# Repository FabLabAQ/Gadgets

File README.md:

# PCBs courtesy of [CMT Energia Dinamica](http://www.cmtenergiadinamica.it/)

## [Tutorial italiano](http://www.fablaquila.org/tutorial/come-assemblare-spille-circuito/)
## [English tutorial](https://create.arduino.cc/projecthub/fablabaq/led-matrix-display-badge-280cfb?ref=team&ref_id=fablabaq&offset=0)

## ATtiny LoRa Node
### top

### bottom

## Ladybug bristlebot

### Final version images

### top

### bottom

## Kids LED badge

### top

### bottom

## LED matrix badge with ATtiny

### top

### bottom

## ATtiny DIY badge

### top

### bottom

## LED matrix printable PCB

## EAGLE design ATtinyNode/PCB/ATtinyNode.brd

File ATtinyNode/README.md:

# ATtiny LoRa node 

A minimal ATtiny85-based LoRaWAN node

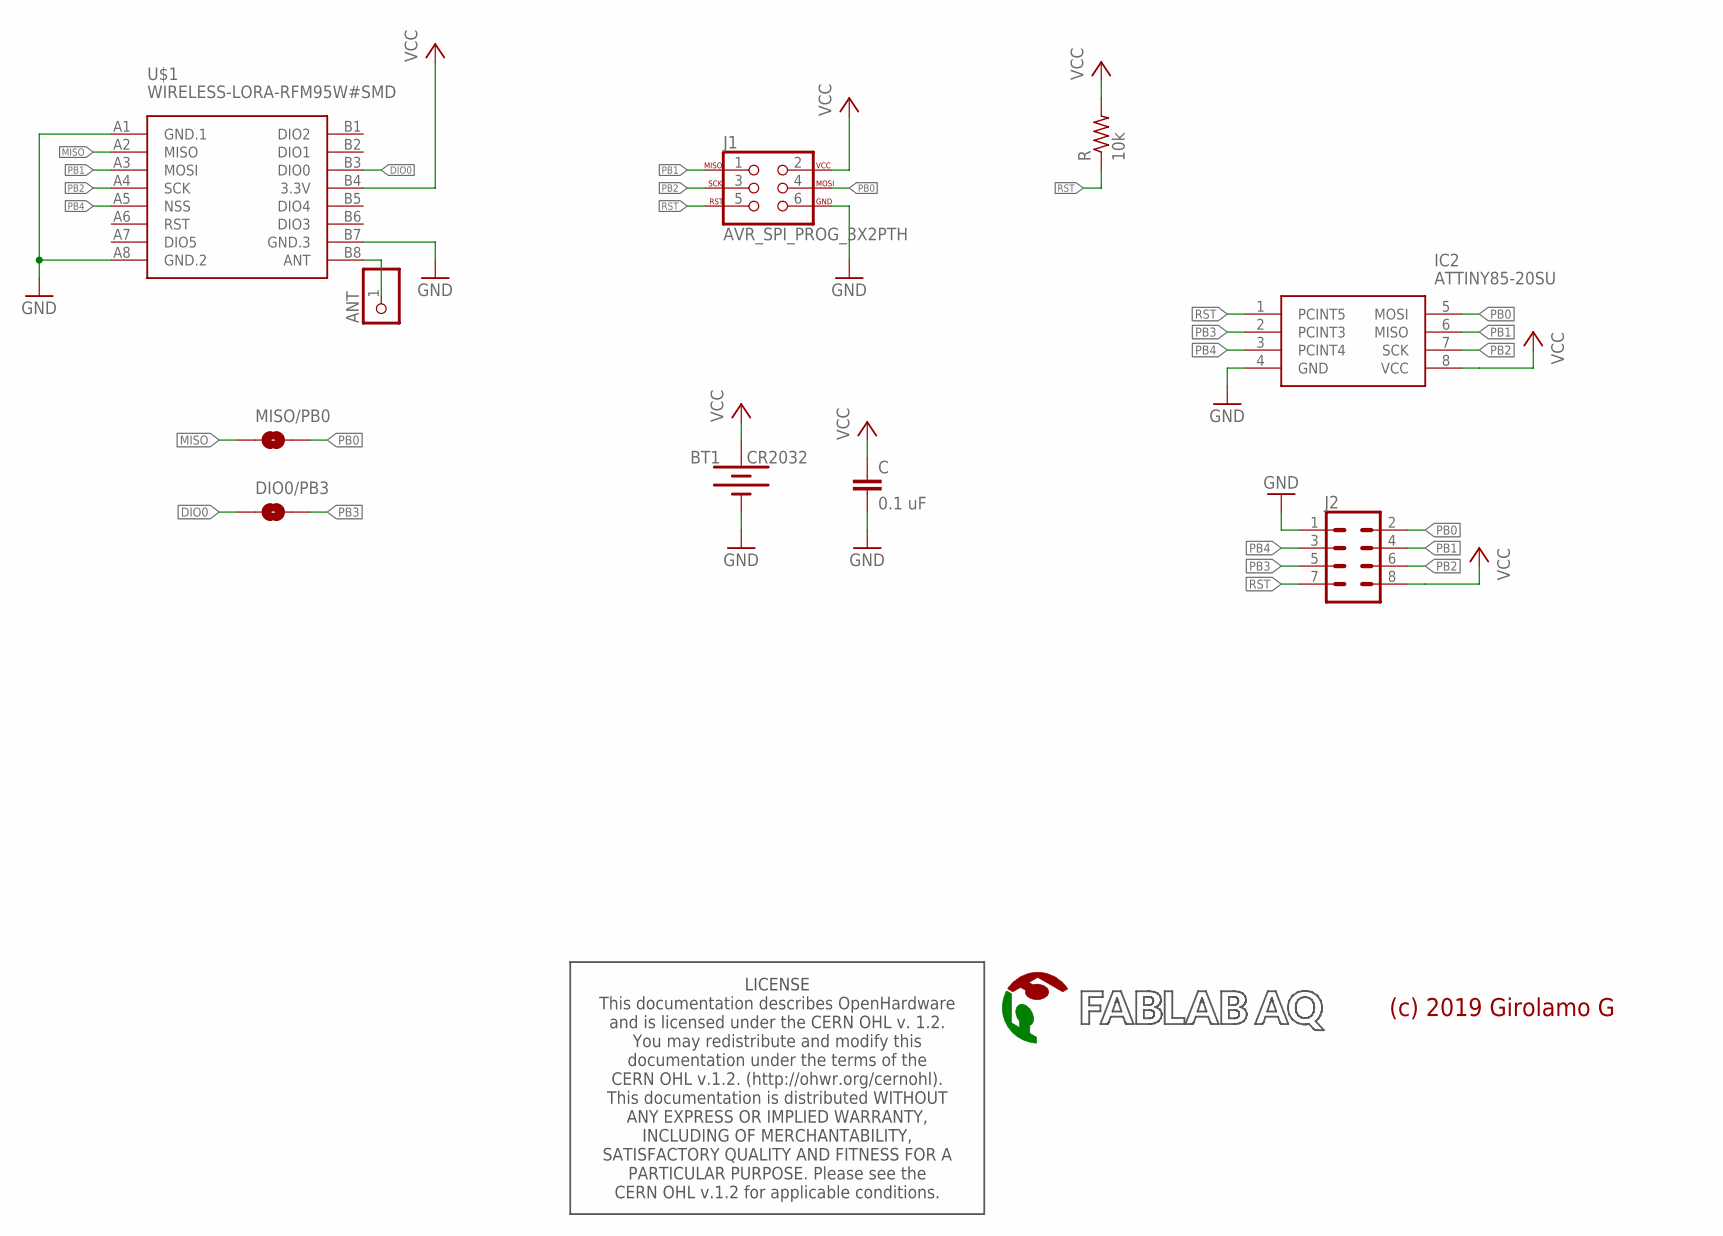
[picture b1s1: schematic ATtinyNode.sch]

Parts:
ANT: PINHD-1X1CB; 1X01-CLEANBIG
BT1: CR2032; BATTCOM_20MM_PTH
C: 0.1 uF; C0805
DIO0/PB3: JUMPER-SMT_2_NO_SILK; SMT-JUMPER_2_NO_SILK
IC2: ATTINY85-20SU; SOT127P798X216-8N
J1: AVR_SPI_PROG_3X2PTH; 2X3
J2: CONN_04X2; 2X4
MISO/PB0: JUMPER-SMT_2_NO_SILK; SMT-JUMPER_2_NO_SILK
R: 10k; R0805
U$1: WIRELESS-LORA-RFM95W#SMD
U$2: FABLABAQ_LOGONONE; NONE
U$3: CERN_OHL_1.2; DOC_CERN_OHL_1.2

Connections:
ANT: ANT.1, U$1.B8 (ANT)
DIO0: DIO0/PB3.1, U$1.B3 (DIO0)
GND: BT1.2 (-), C.2, IC2.4 (GND), J1.6, J2.1, U$1.A1 (GND.1), U$1.A8 (GND.2), U$1.B7 (GND.3)
MISO: MISO/PB0.1, U$1.A2 (MISO)
PB0: IC2.5 (MOSI), J1.4, J2.2, MISO/PB0.2
PB1: IC2.6 (MISO), J1.1, J2.4, U$1.A3 (MOSI)
PB2: IC2.7 (SCK), J1.3, J2.6, U$1.A4 (SCK)
PB3: DIO0/PB3.2, IC2.2 (PCINT3), J2.5
PB4: IC2.3 (PCINT4), J2.3, U$1.A5 (NSS)
RST: IC2.1 (PCINT5), J1.5, J2.7, R.1
VCC: BT1.1 (+), C.1, IC2.8 (VCC), J1.2, J2.8, R.2, U$1.B4 (3.3V)

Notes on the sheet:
(c) 2019 Girolamo G

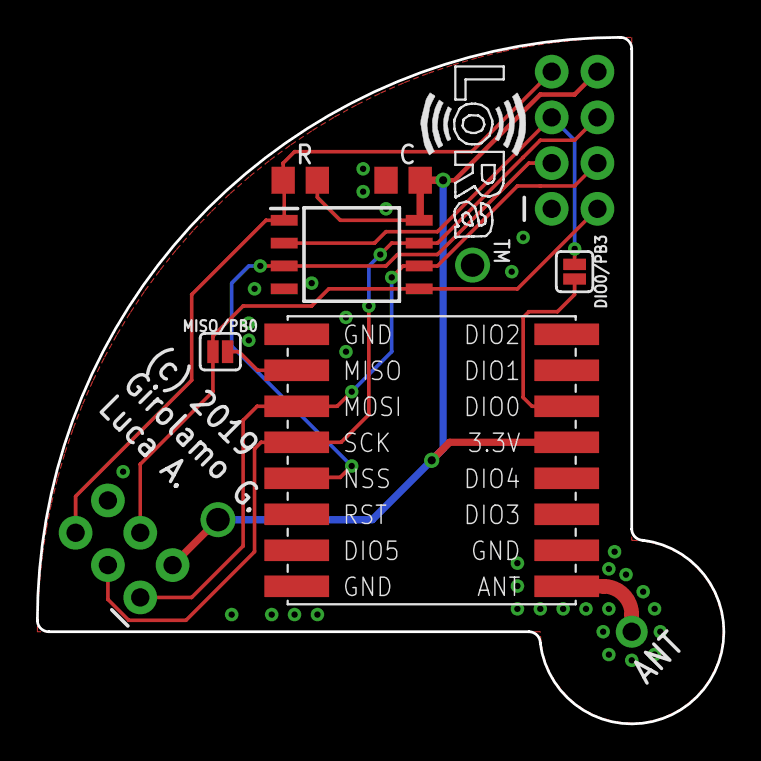
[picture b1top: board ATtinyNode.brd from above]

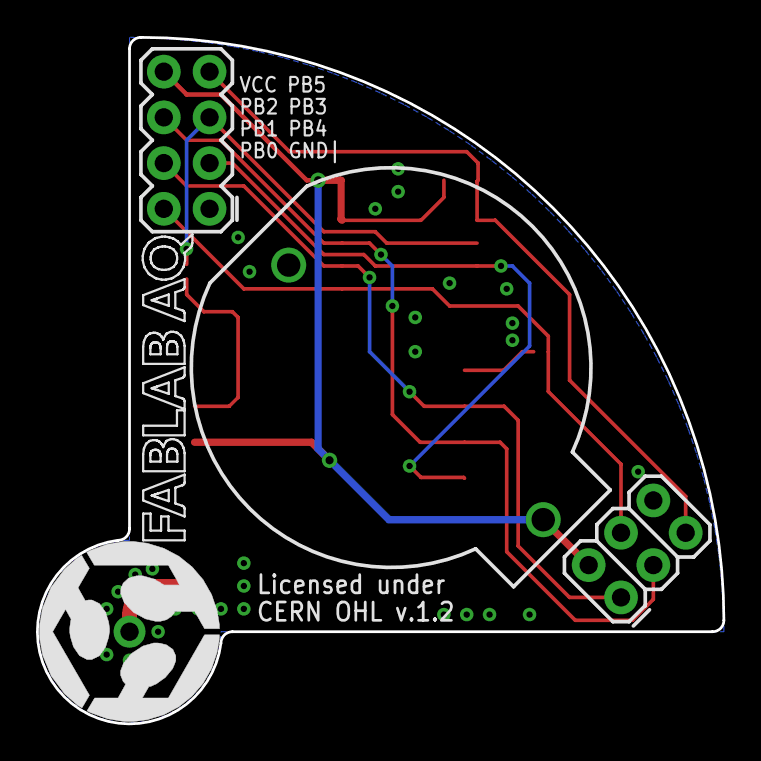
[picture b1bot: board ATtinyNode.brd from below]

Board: 2 copper layers, 38.1 x 38.1 mm, 12 parts (4 on the bottom side), 11 nets.

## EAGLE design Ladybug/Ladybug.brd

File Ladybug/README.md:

## Ladybug bristlebot

### Final version images

### top

### bottom

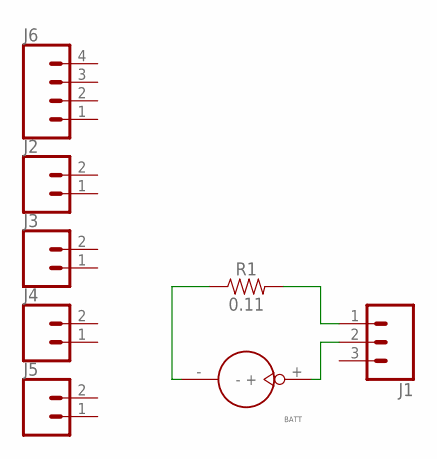
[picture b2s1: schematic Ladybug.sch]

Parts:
BATT: BATTERY_1236_C
J1: CONN_03LOCK; 1X03_LOCK
J2, J3, J4, J5: CONN_02; 1X02
J6: CONN_04; 1X04
R1: 0.11; 2010

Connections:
unnamed: BATT.-, R1.1
unnamed: J1.1, R1.2
unnamed: BATT.+, J1.2

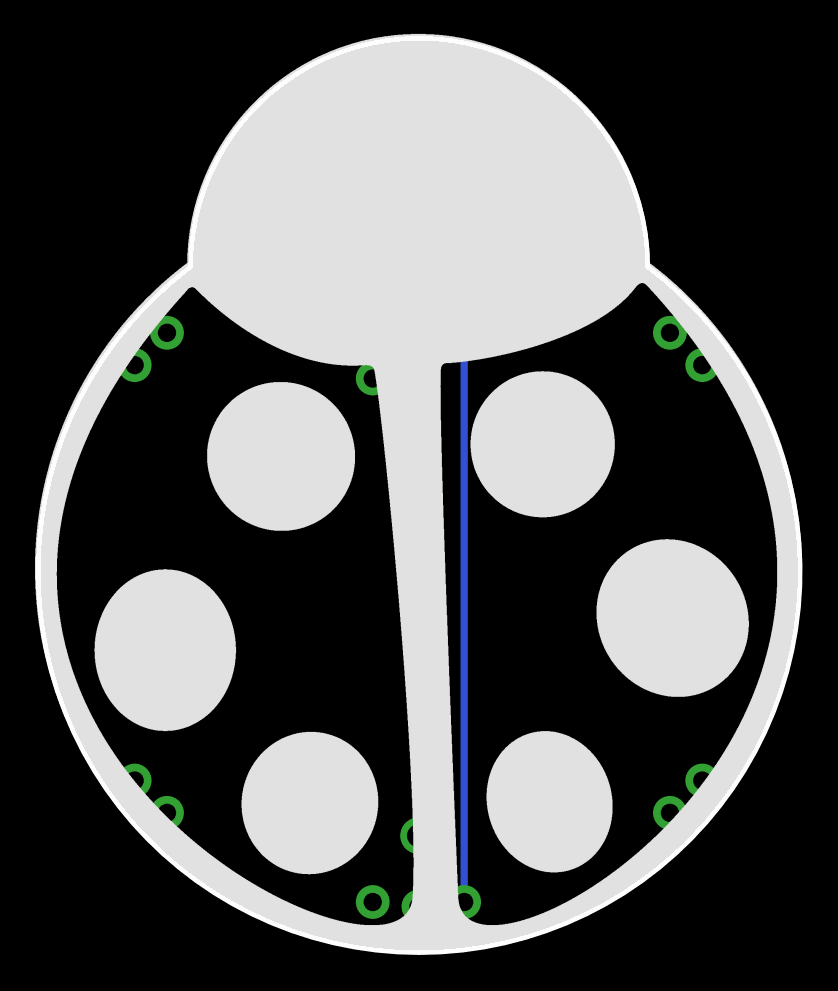
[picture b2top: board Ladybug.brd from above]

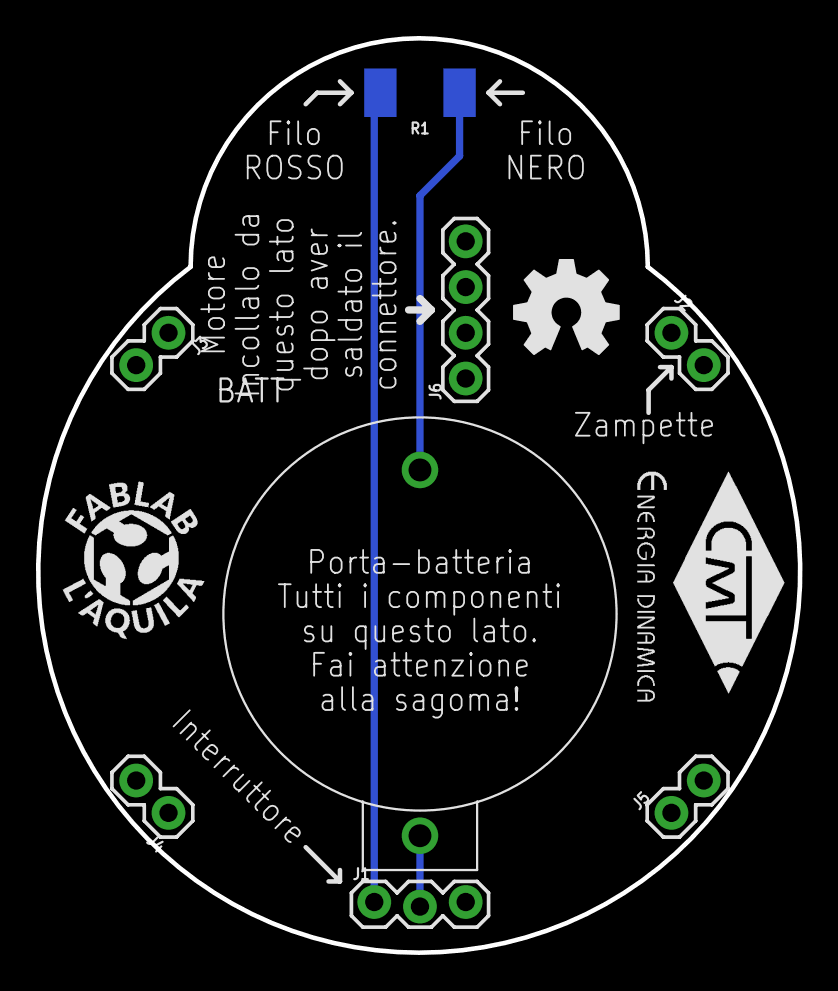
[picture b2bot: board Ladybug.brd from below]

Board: 2 copper layers, 42.3 x 50.8 mm, 8 parts (8 on the bottom side), 3 nets.

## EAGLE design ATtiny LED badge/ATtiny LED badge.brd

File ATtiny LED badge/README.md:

Use https://github.com/MCUdude/MicroCore with Arduino IDE.

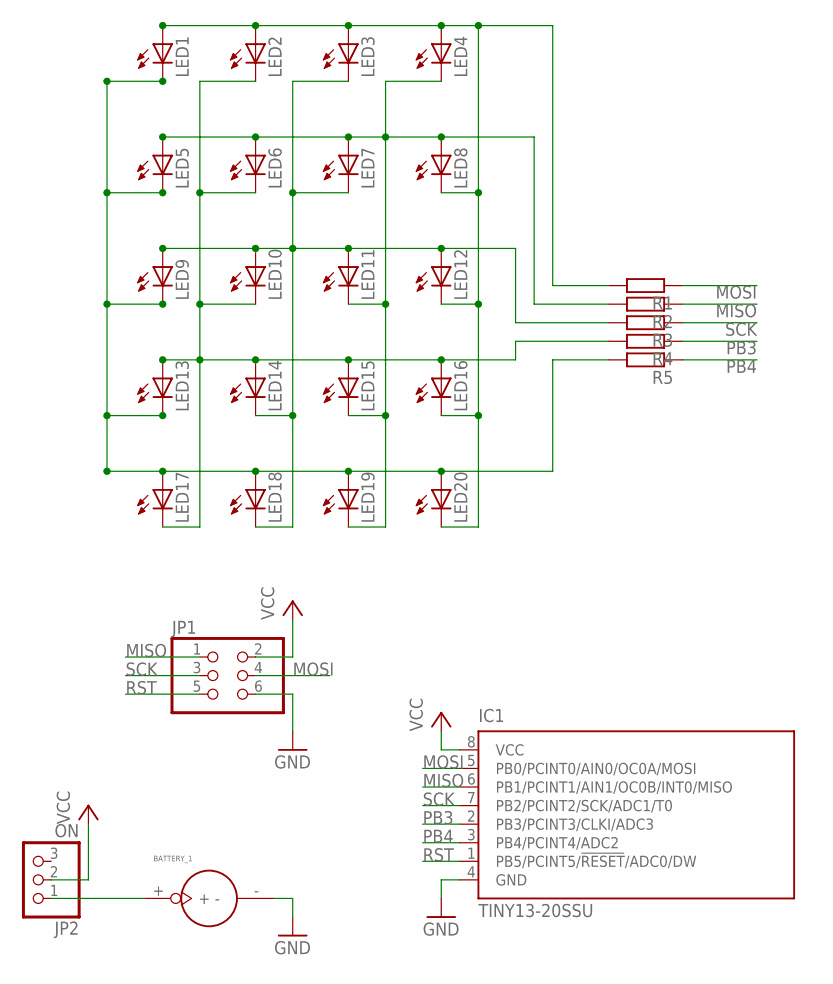
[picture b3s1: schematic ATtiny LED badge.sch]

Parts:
BATTERY_1: BATTERY_1236_C
IC1: TINY13-20SSU; 8S1
JP1: PINHD-2X3; 2X03
JP2: ON; 1X03
LED1, LED2, LED3, LED4, LED5, LED6, LED7, LED8, LED9, LED10, LED11, LED12, LED13, LED14, LED15, LED16, LED17, LED18, LED19, LED20: LED3MM
R1, R2, R3, R4, R5: R-EU_0207/7; 0207/7

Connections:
GND: BATTERY_1.-, IC1.4 (GND), JP1.6
MISO: IC1.6 (PB1/PCINT1/AIN1/OC0B/INT0/MISO), JP1.1, R2.1
MOSI: IC1.5 (PB0/PCINT0/AIN0/OC0A/MOSI), JP1.4, R1.1
unnamed: LED1.A, LED2.A, LED3.A, LED4.A, LED8.K (C), LED12.K (C), LED16.K (C), LED20.K (C), R1.2
unnamed: LED4.K (C), LED5.A, LED6.A, LED7.A, LED8.A, LED11.K (C), LED15.K (C), LED19.K (C), R2.2
unnamed: LED3.K (C), LED7.K (C), LED9.A, LED10.A, LED11.A, LED12.A, LED14.K (C), LED18.K (C), R3.2
unnamed: LED2.K (C), LED6.K (C), LED10.K (C), LED13.A, LED14.A, LED15.A, LED16.A, LED17.K (C), R4.2
unnamed: LED1.K (C), LED5.K (C), LED9.K (C), LED13.K (C), LED17.A, LED18.A, LED19.A, LED20.A, R5.2
unnamed: BATTERY_1.+, JP2.1
PB3: IC1.2 (PB3/PCINT3/CLKI/ADC3), R4.1
PB4: IC1.3 (PB4/PCINT4/ADC2), R5.1
RST: IC1.1 (PB5/PCINT5/!RESET!/ADC0/DW), JP1.5
SCK: IC1.7 (PB2/PCINT2/SCK/ADC1/T0), JP1.3, R3.1
VCC: IC1.8 (VCC), JP1.2, JP2.2

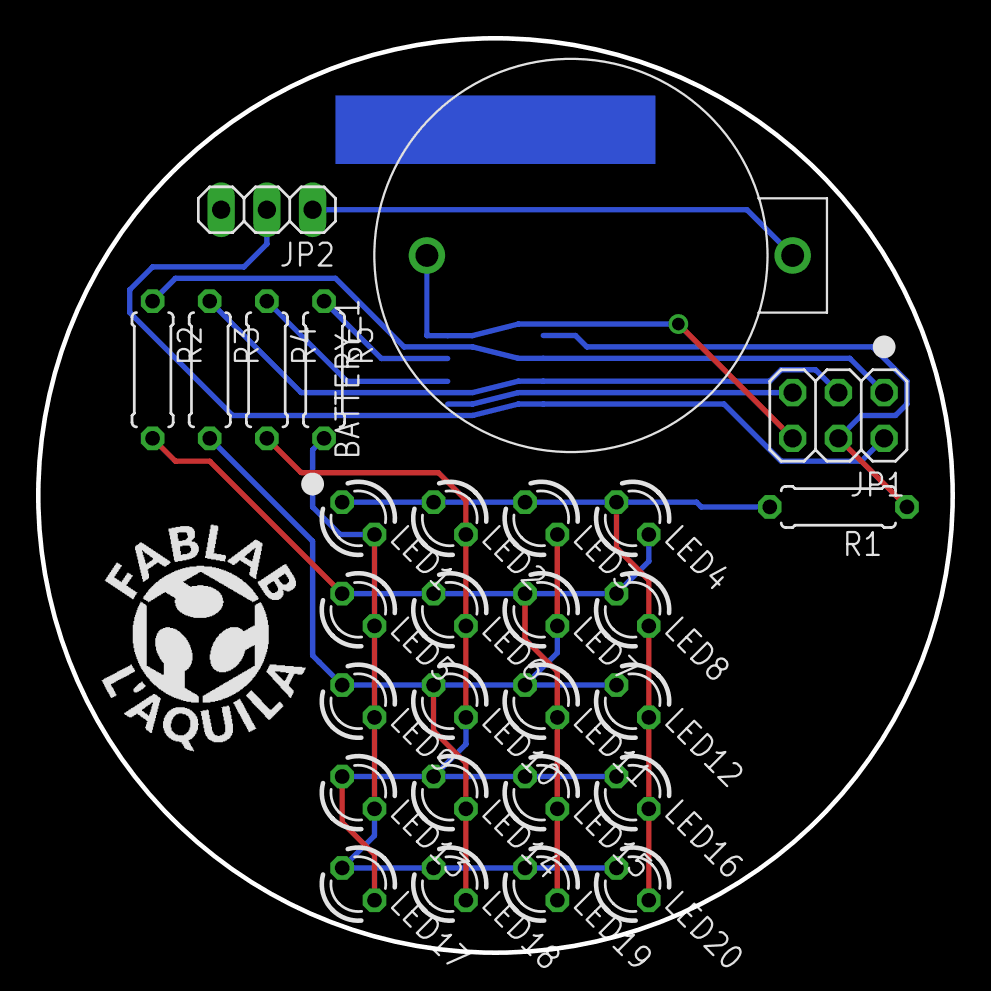
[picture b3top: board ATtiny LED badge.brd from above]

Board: 2 copper layers, 50.8 x 50.8 mm, 29 parts (1 on the bottom side), 14 nets.

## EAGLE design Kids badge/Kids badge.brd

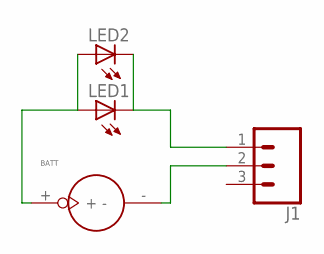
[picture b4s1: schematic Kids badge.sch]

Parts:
BATT: BATTERY_1236_C
J1: CONN_03LOCK; 1X03_LOCK
LED1, LED2: LED5MM

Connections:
unnamed: BATT.+, LED1.A, LED2.A
unnamed: J1.1, LED1.K (C), LED2.K (C)
unnamed: BATT.-, J1.2

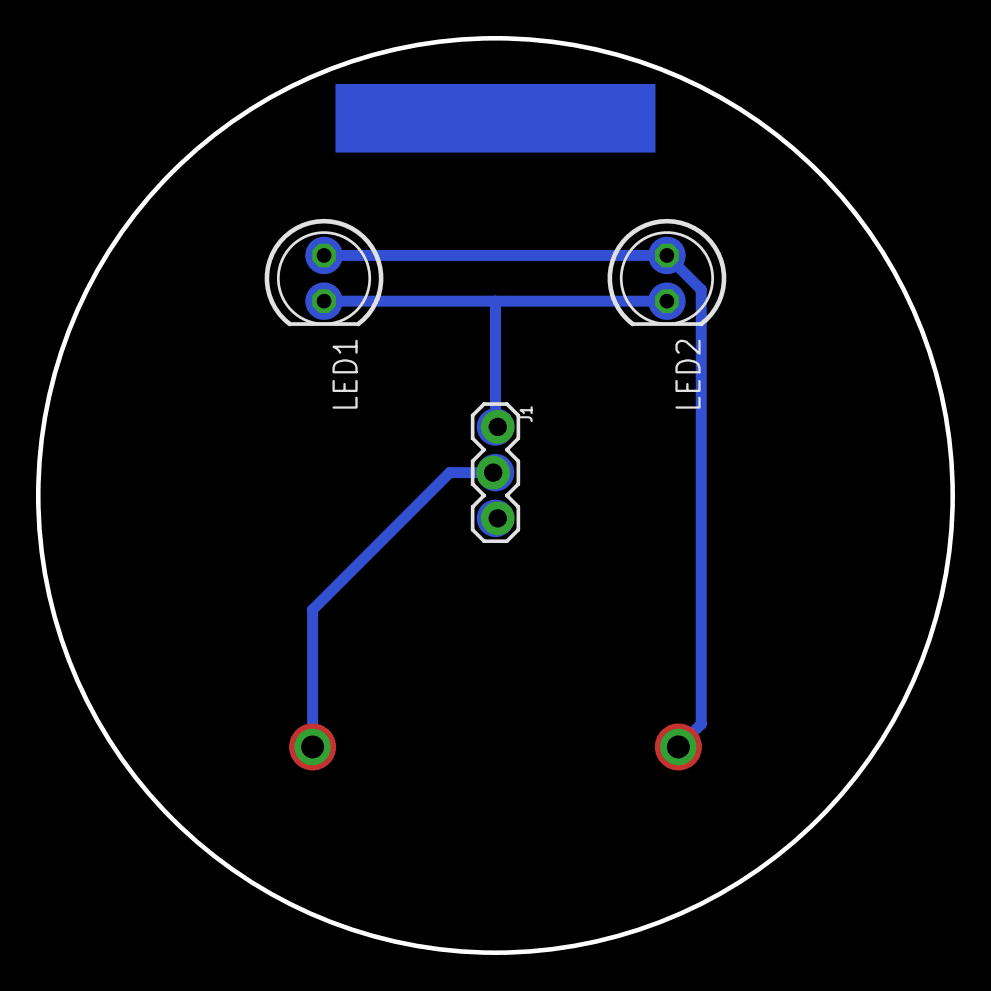
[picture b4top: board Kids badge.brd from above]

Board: 2 copper layers, 50.8 x 50.8 mm, 4 parts (1 on the bottom side), 3 nets.

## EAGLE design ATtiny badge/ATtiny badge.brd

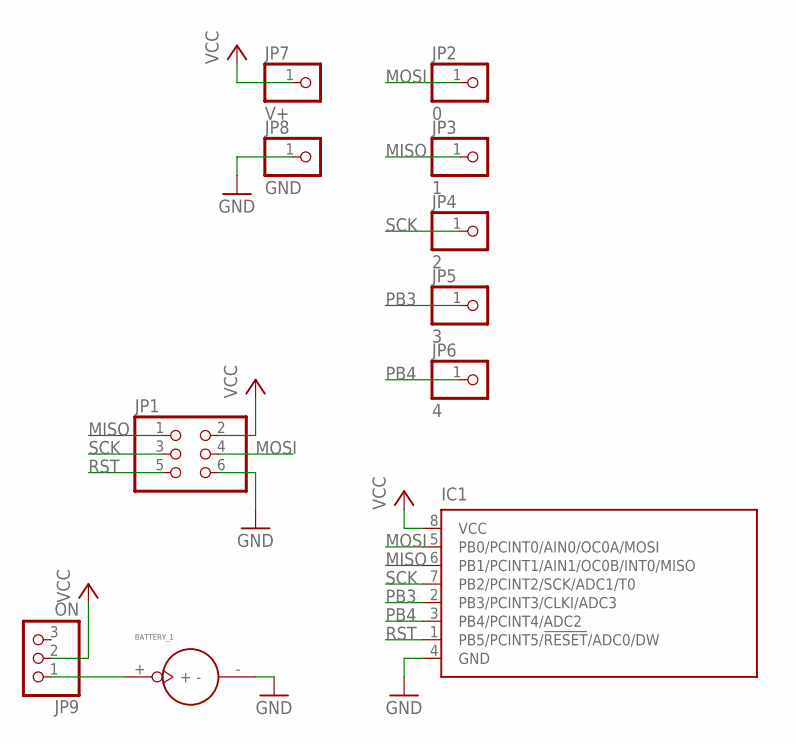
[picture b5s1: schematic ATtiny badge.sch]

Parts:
BATTERY_1: BATTERY_1236_C
IC1: TINY13-20SU; 8S2
JP1: PINHD-2X3; 2X03
JP2: 0; 1X01
JP3: 1; 1X01
JP4: 2; 1X01
JP5: 3; 1X01
JP6: 4; 1X01
JP7: V+; 1X01
JP8: GND; 1X01
JP9: ON; 1X03

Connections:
GND: BATTERY_1.-, IC1.4 (GND), JP1.6, JP8.1
MISO: IC1.6 (PB1/PCINT1/AIN1/OC0B/INT0/MISO), JP1.1, JP3.1
MOSI: IC1.5 (PB0/PCINT0/AIN0/OC0A/MOSI), JP1.4, JP2.1
unnamed: BATTERY_1.+, JP9.1
PB3: IC1.2 (PB3/PCINT3/CLKI/ADC3), JP5.1
PB4: IC1.3 (PB4/PCINT4/ADC2), JP6.1
RST: IC1.1 (PB5/PCINT5/!RESET!/ADC0/DW), JP1.5
SCK: IC1.7 (PB2/PCINT2/SCK/ADC1/T0), JP1.3, JP4.1
VCC: IC1.8 (VCC), JP1.2, JP7.1, JP9.2

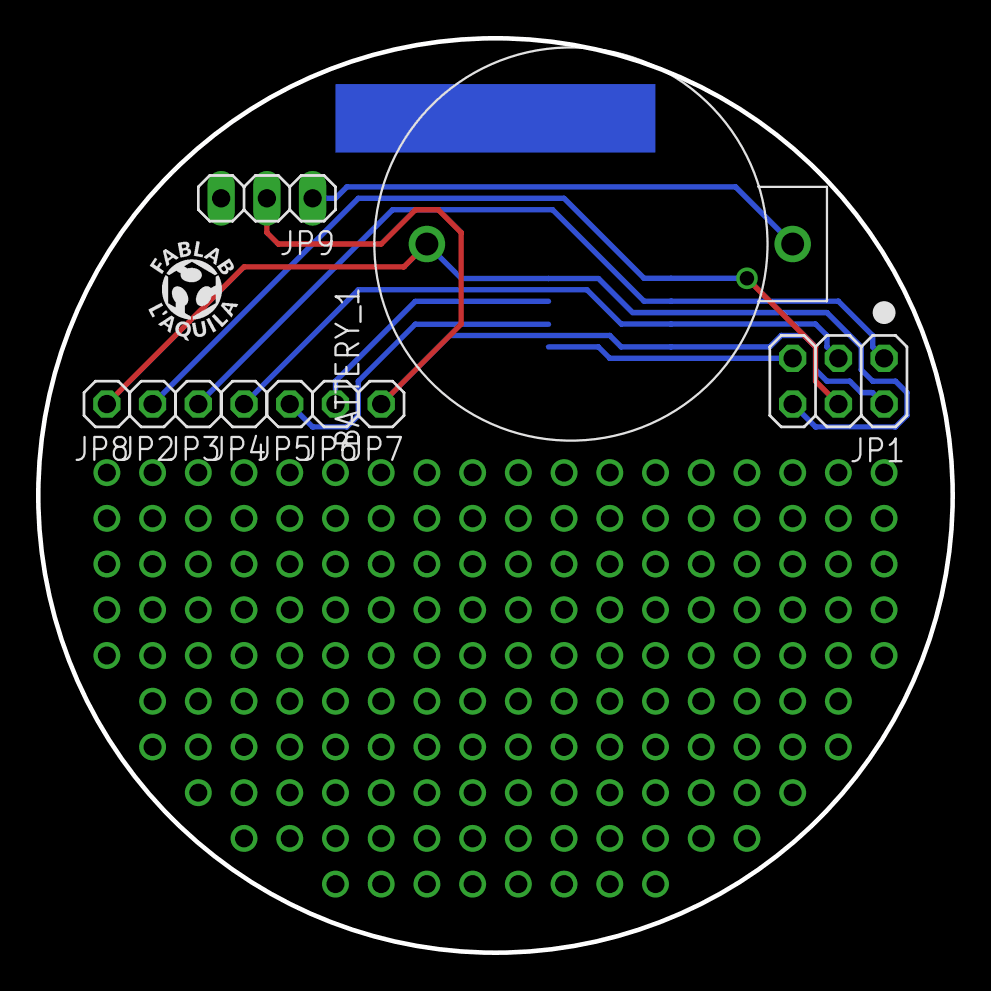
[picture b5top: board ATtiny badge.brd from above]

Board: 2 copper layers, 50.8 x 50.8 mm, 11 parts (1 on the bottom side), 9 nets.

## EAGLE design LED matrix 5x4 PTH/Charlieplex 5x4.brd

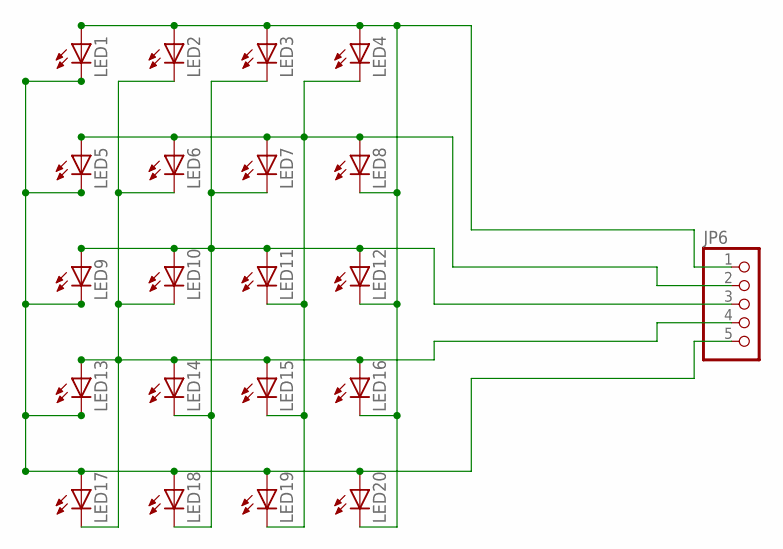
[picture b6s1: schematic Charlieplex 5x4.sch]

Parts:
JP6: PINHD-1X5; 1X05
LED1, LED2, LED3, LED4, LED5, LED6, LED7, LED8, LED9, LED10, LED11, LED12, LED13, LED14, LED15, LED16, LED17, LED18, LED19, LED20: LED3MM

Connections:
unnamed: JP6.1, LED1.A, LED2.A, LED3.A, LED4.A, LED8.K (C), LED12.K (C), LED16.K (C), LED20.K (C)
unnamed: JP6.2, LED4.K (C), LED5.A, LED6.A, LED7.A, LED8.A, LED11.K (C), LED15.K (C), LED19.K (C)
unnamed: JP6.3, LED3.K (C), LED7.K (C), LED9.A, LED10.A, LED11.A, LED12.A, LED14.K (C), LED18.K (C)
unnamed: JP6.4, LED2.K (C), LED6.K (C), LED10.K (C), LED13.A, LED14.A, LED15.A, LED16.A, LED17.K (C)
unnamed: JP6.5, LED1.K (C), LED5.K (C), LED9.K (C), LED13.K (C), LED17.A, LED18.A, LED19.A, LED20.A

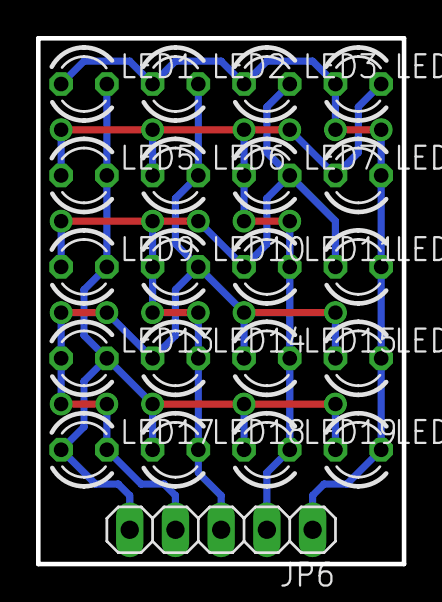
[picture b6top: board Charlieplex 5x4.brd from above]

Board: 2 copper layers, 20.3 x 29.2 mm, 21 parts (0 on the bottom side), 5 nets.

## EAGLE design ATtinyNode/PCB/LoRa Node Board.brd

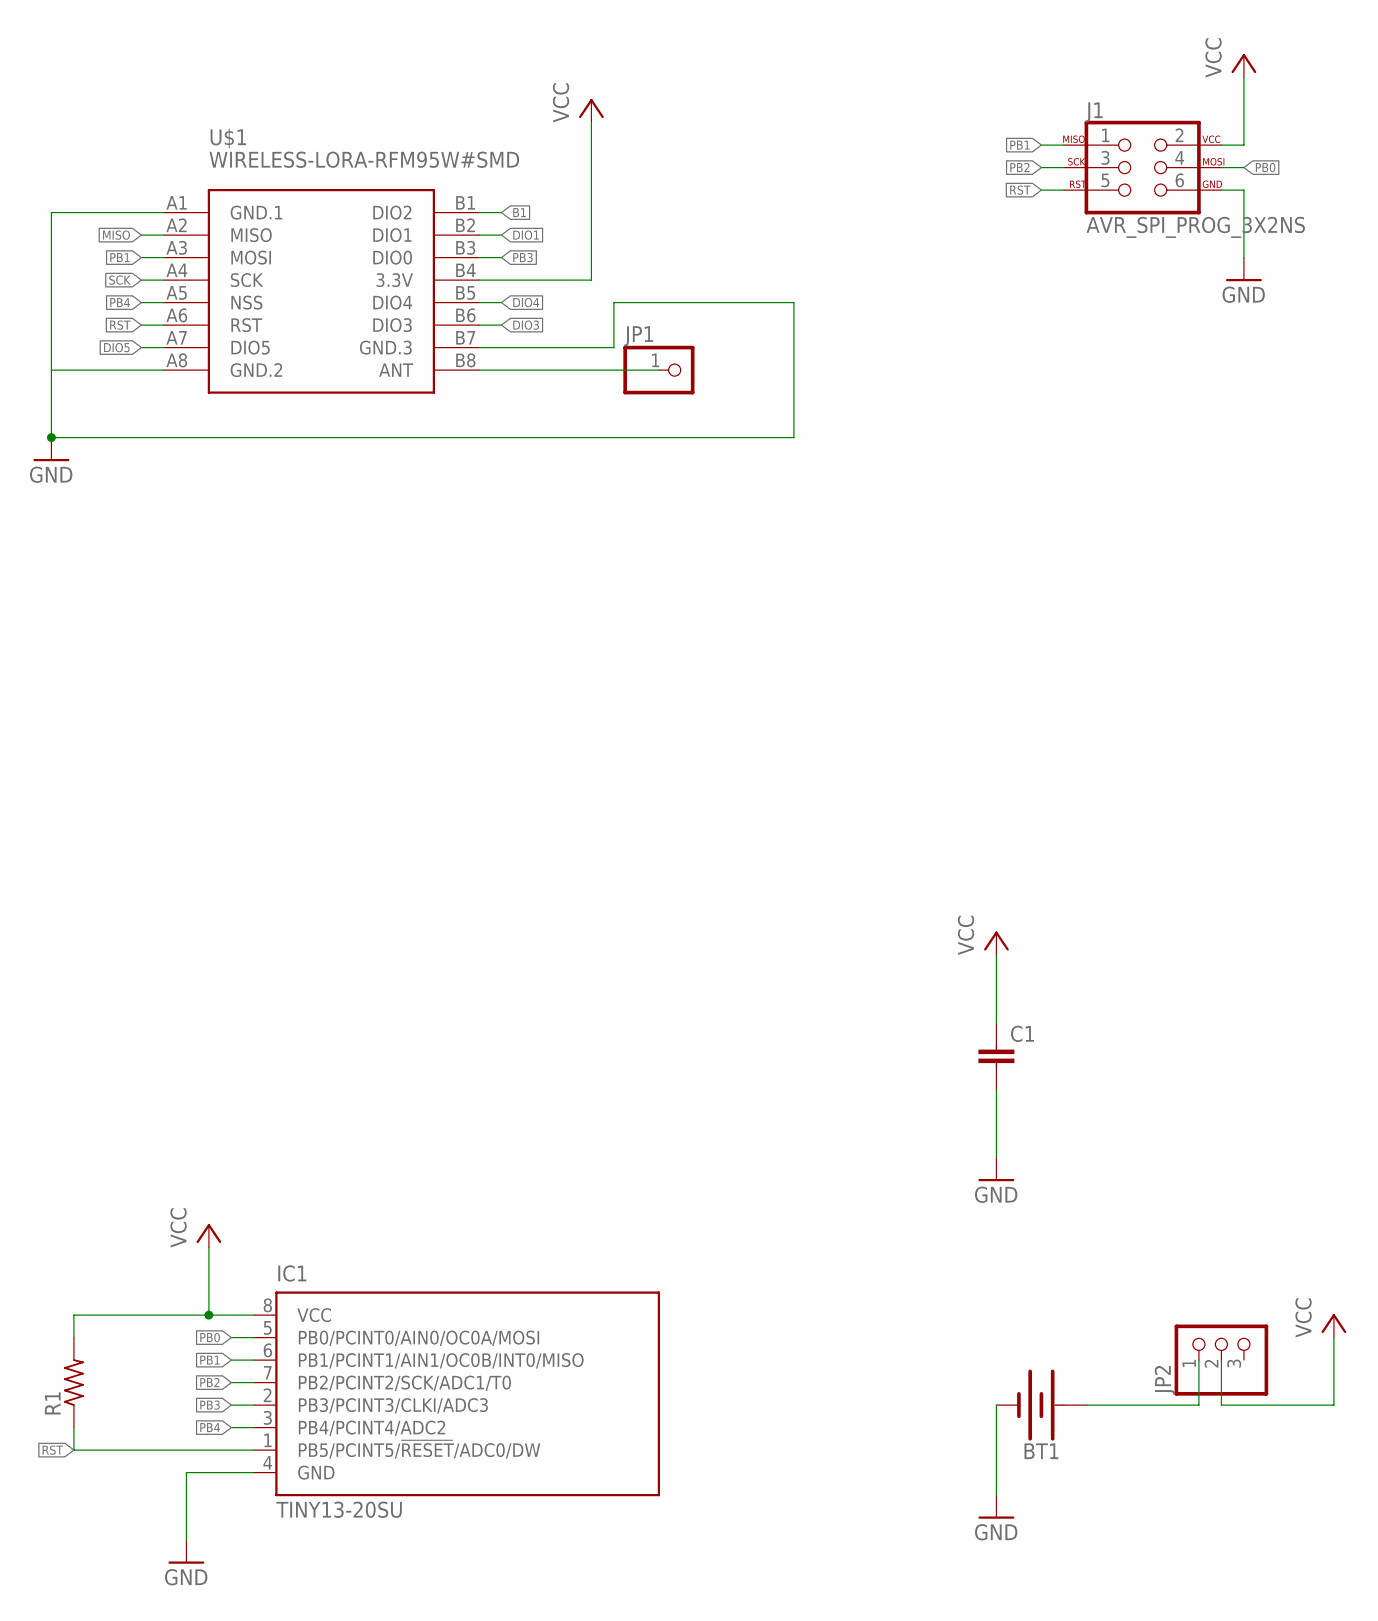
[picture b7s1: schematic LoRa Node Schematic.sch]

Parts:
BT1: BATTERY-20MM_PTH; BATTCOM_20MM_PTH
C1: C-EUC0603; C0603
IC1: TINY13-20SU; 8S2
J1: AVR_SPI_PROG_3X2NS; 2X3-NS
JP1: PINHD-1X1CB; 1X01-CLEANBIG
JP2: PINHD-1X3; 1X03
R1: R-US_R0603; R0603
U$1: WIRELESS-LORA-RFM95W#SMD

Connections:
ANT: JP1.1, U$1.B8 (ANT)
B1: U$1.B1 (DIO2)
DIO1: U$1.B2 (DIO1)
DIO3: U$1.B6 (DIO3)
DIO4: U$1.B5 (DIO4)
DIO5: U$1.A7 (DIO5)
GND: BT1.2 (-), C1.2, IC1.4 (GND), J1.6, U$1.A1 (GND.1), U$1.A8 (GND.2), U$1.B7 (GND.3)
MISO: U$1.A2 (MISO)
unnamed: BT1.1 (+), JP2.1
PB0: IC1.5 (PB0/PCINT0/AIN0/OC0A/MOSI), J1.4
PB1: IC1.6 (PB1/PCINT1/AIN1/OC0B/INT0/MISO), J1.1, U$1.A3 (MOSI)
PB2: IC1.7 (PB2/PCINT2/SCK/ADC1/T0), J1.3
PB3: IC1.2 (PB3/PCINT3/CLKI/ADC3), U$1.B3 (DIO0)
PB4: IC1.3 (PB4/PCINT4/ADC2), U$1.A5 (NSS)
RST: IC1.1 (PB5/PCINT5/!RESET!/ADC0/DW), J1.5, R1.1, U$1.A6 (RST)
SCK: U$1.A4 (SCK)
VCC: C1.1, IC1.8 (VCC), J1.2, JP2.2, R1.2, U$1.B4 (3.3V)

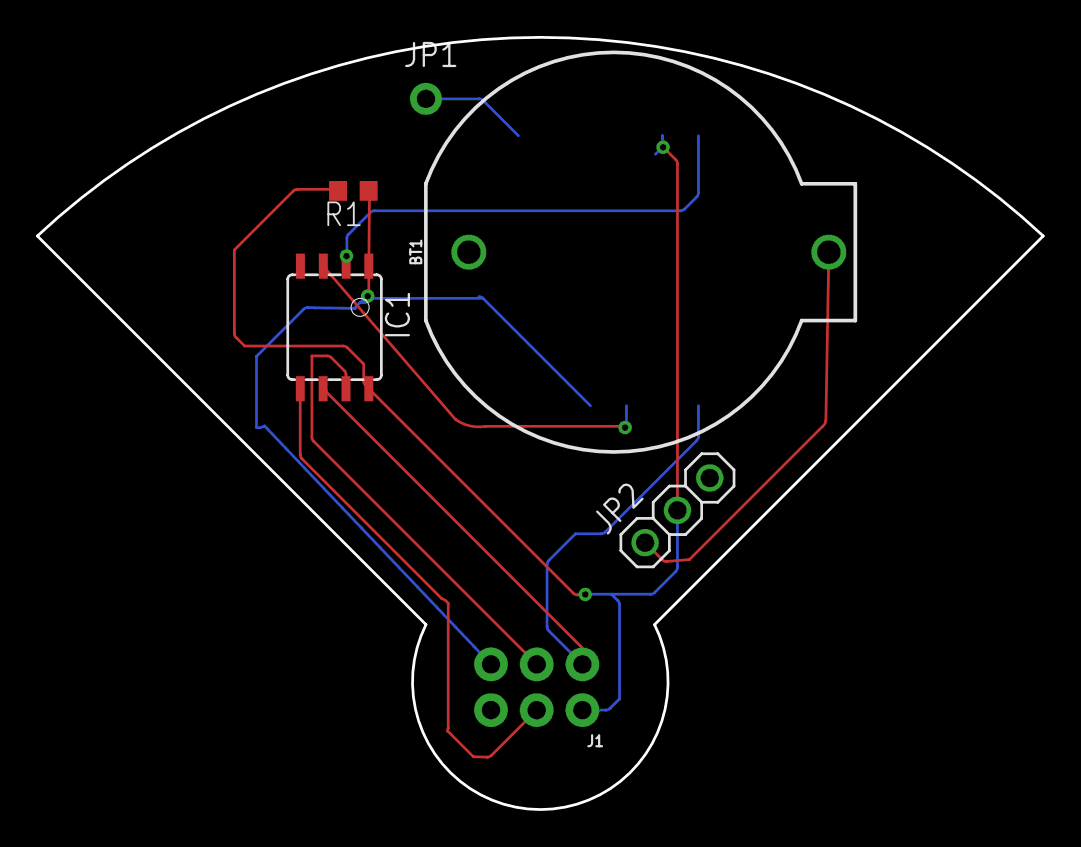
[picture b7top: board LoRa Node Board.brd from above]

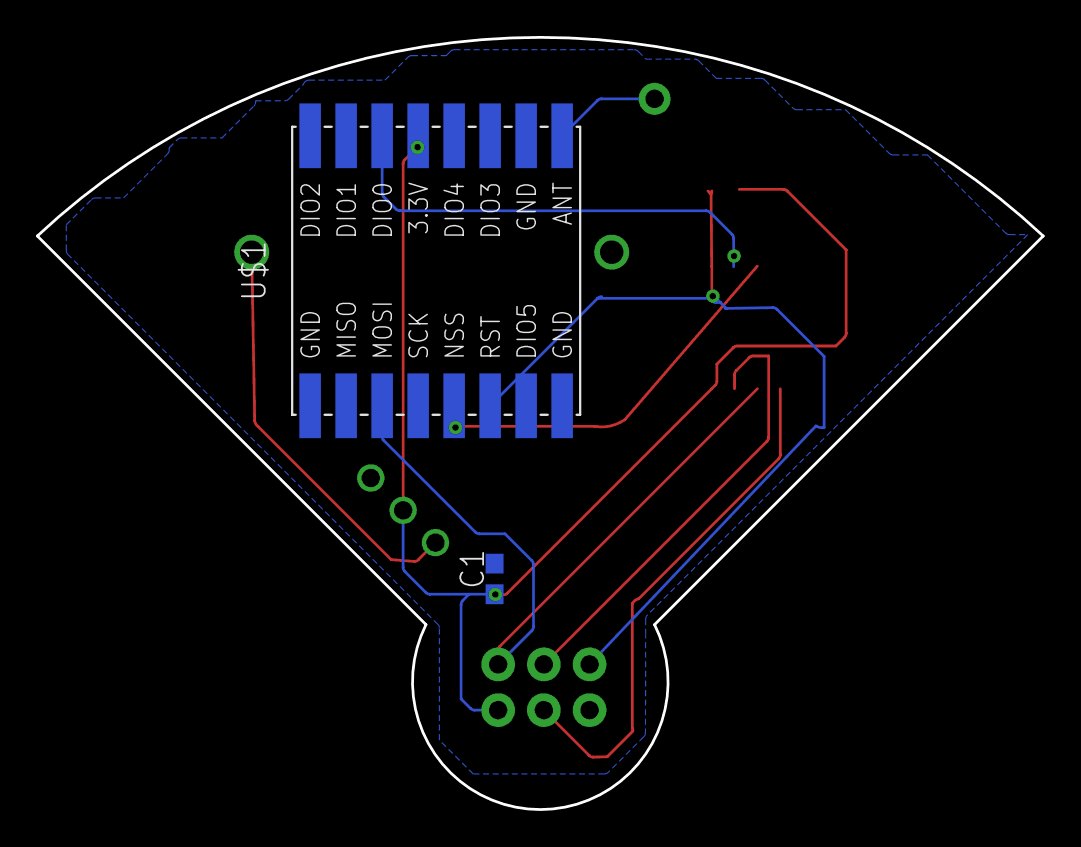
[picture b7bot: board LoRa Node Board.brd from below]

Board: 2 copper layers, 55.9 x 42.9 mm, 8 parts (2 on the bottom side), 10 nets.

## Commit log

2016-08-14 new badges
2016-08-14 added boards images
2016-08-16 Inseriti le giunzioni mancanti nello schema
2016-08-16 corrected board
2016-08-16 sketck v0.2
2016-08-18 routed PCBs
2016-08-21 renderings + gerbers
2016-08-22 new PCB
2016-08-25 Added logos
2016-08-25 Removed holes too close from edge
2016-08-28 final version
2016-09-28 charlie
2016-10-13 updated tutorial URL
2016-10-29 new sketch
2017-07-03 ladybug
2017-07-03 readme
2017-07-04 Modifieg silkscreen decorations
2017-07-04 Removed eyes placeholder
2017-07-05 Ladybug silkscreen use only one layer. Readded dimension layer.
2017-07-05 Removed eyes placeholder. Reallineated Silkscreen with bottom layer.
2017-07-05 Removed sporious wire.
2017-09-09 added attiny13 support
2017-09-25 Added photo and video.
2017-09-25 Converted mp4 to gif
2017-09-25 Added README
2017-09-25 Fixed README path typo
2017-12-05 updated to ATtiny13
2019-02-16 ATtinyNode
2019-02-18 Add files via upload
    Added LoRa node PCB
2019-02-19 ATtinyNode review

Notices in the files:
ATtinyNode/PCB/ATtinyNode.brd:
Licensed under
CERN OHL v.1.2
parts and their libraries:
SparkFun-Batteries: Licensing: Creative Commons ShareAlike 4.0 International - https://creativecommons.org/licenses/by-sa/4.0
diy-modules: Released under the Creative Commons Attribution 4.0 International License: http://creativecommons.org/licenses/by/4.0
